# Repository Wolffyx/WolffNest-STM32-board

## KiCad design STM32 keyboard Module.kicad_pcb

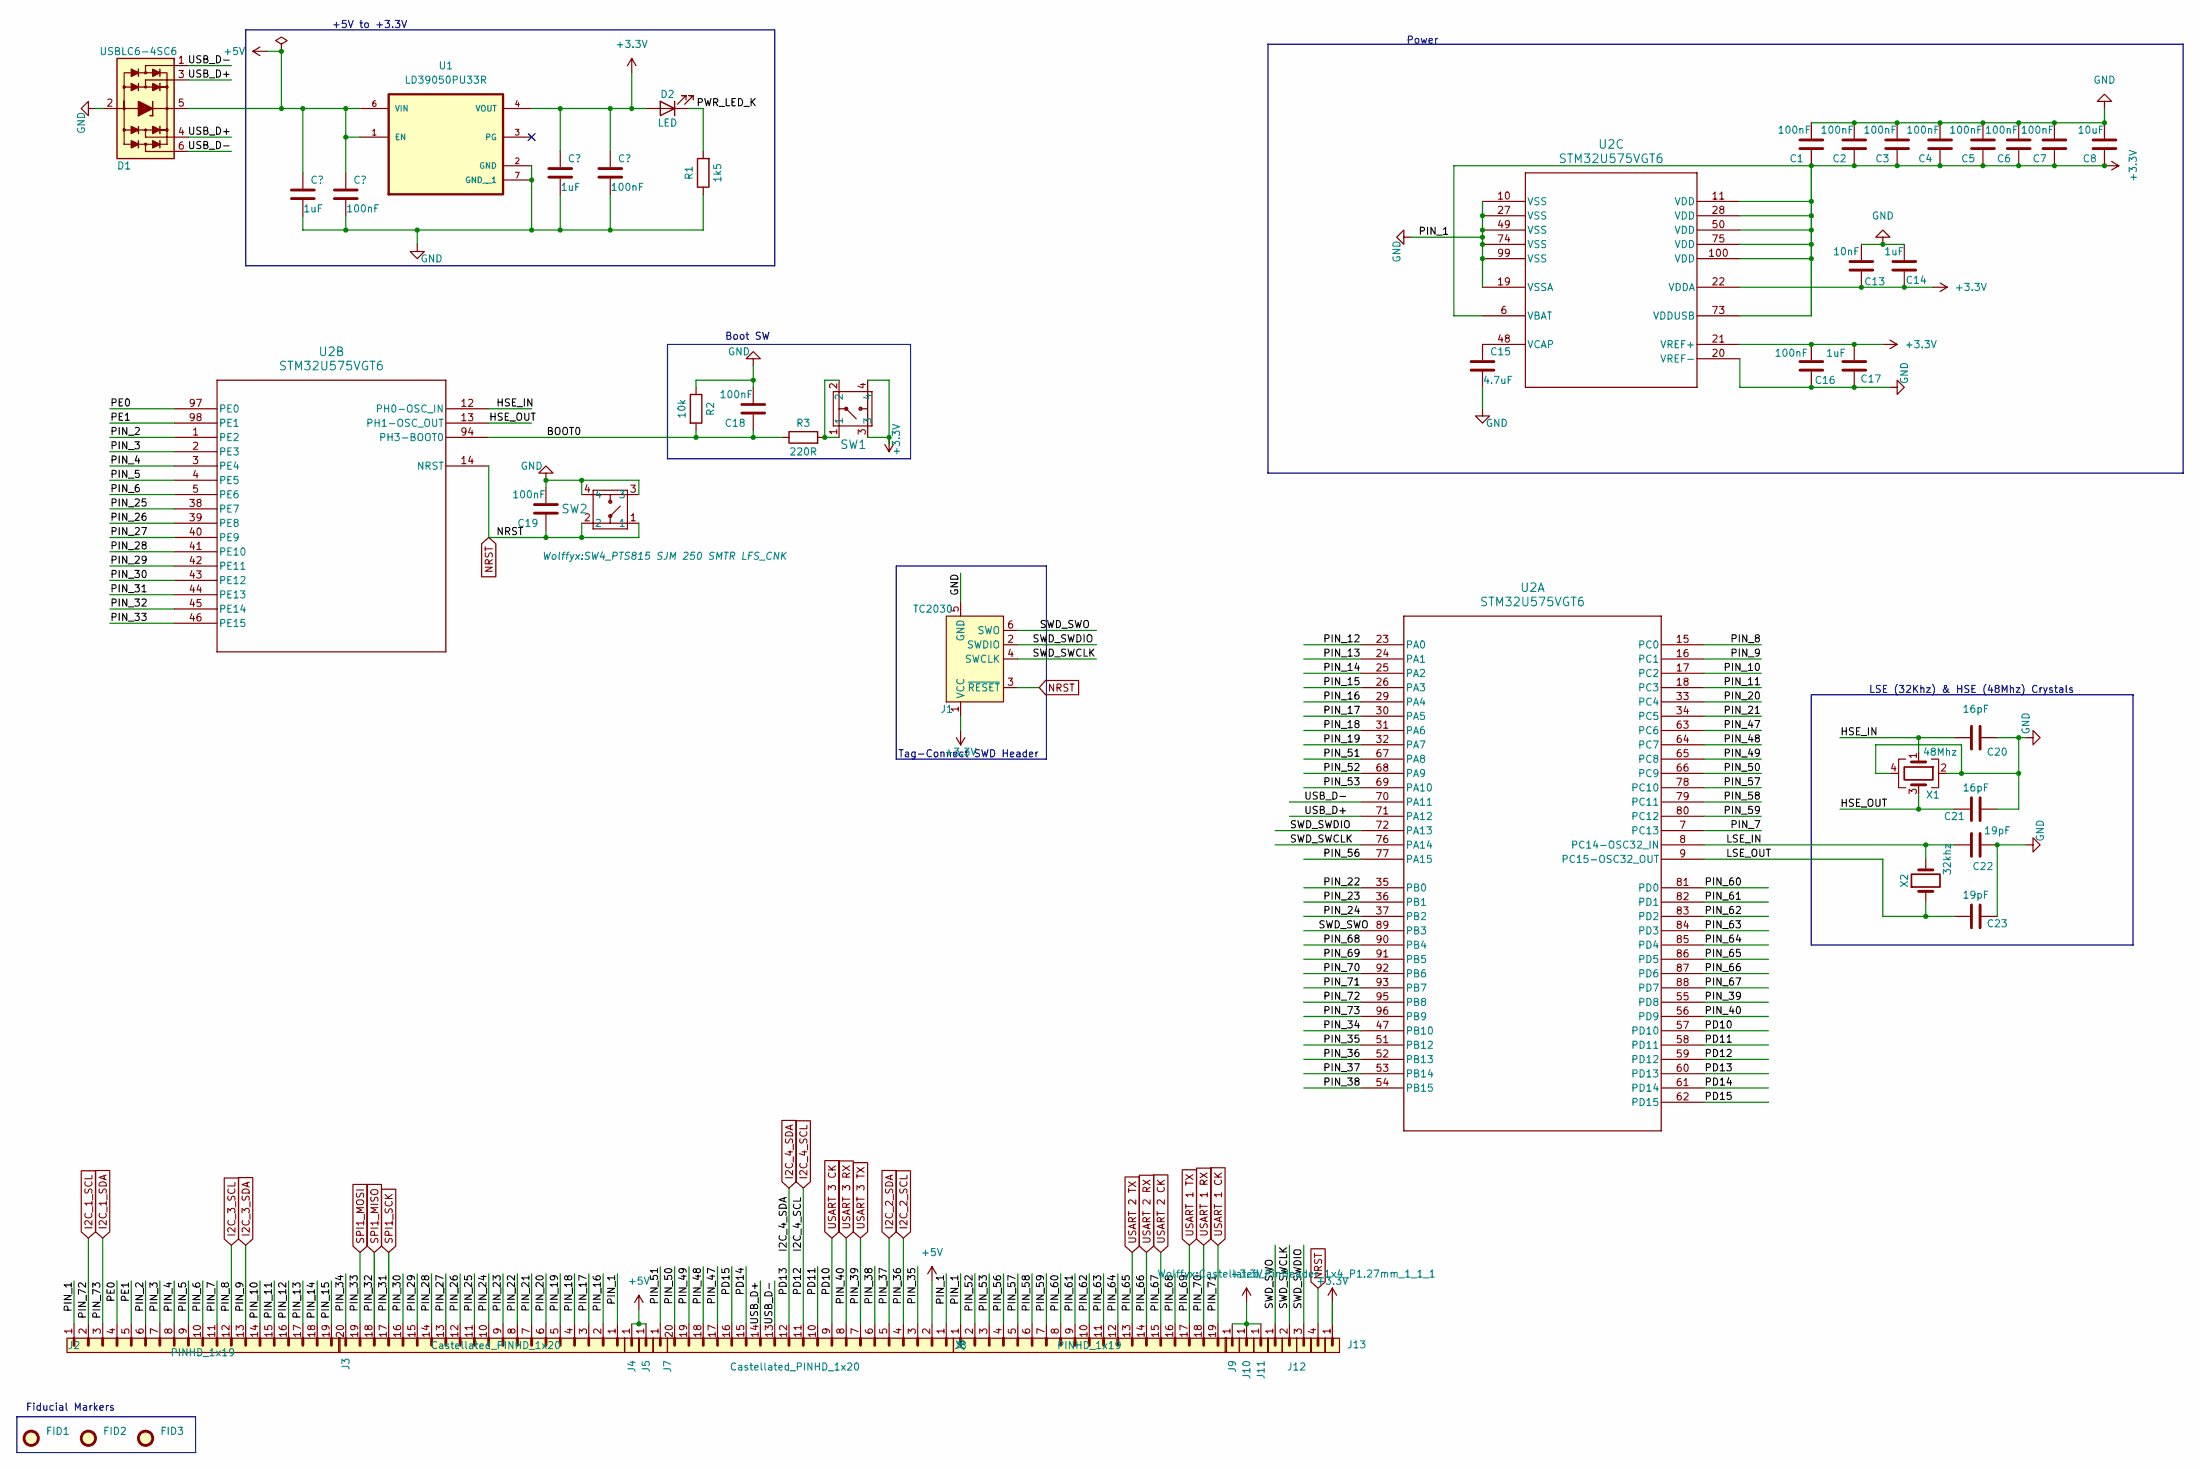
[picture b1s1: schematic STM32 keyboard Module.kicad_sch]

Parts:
C1, C2, C3, C4, C5, C6, C7, C10, C12, C16, C18, C19: 100nF; C_0402_1005Metric; Manufacturer Part No 0402ZD104KAT2A
C8: 10uF; C_0603_1608Metric; Manufacturer Part No CL10A106MQ8NNNC
C9, C11, C14: 1uF; C_0603_1608Metric; Manufacturer Part No CL10B105KQ8NNNC
C13: 10nF; C_0603_1608Metric; Manufacturer Part No CL10B103KB85PND
C15: 4.7uF; C_0603_1608Metric; Manufacturer Part No CL10A475KO8NNNC
C17: 1uF; C_0603_1608Metric; Manufacturer Part No CL10A106MQ8NNNC
C20, C21: 16pF; C_0402_1005Metric; Manufacturer Part No GCM1555C1H160FA16D
C22, C23: 19pF; C_0402_1005Metric; Manufacturer Part No GJM1555C1H190FB01D
D1: USBLC6-4SC6; SOT23-6L_STM; Manufacturer Part No USBLC6-4SC6
D2: LED; LED_0402_1005Metric; Manufacturer Part No SML-P12VTT86R
FID1, FID2, FID3: Fiducial; Fiducial_0.5mm_Mask1.5mm
J1: TC2030; Tag-Connect_TC2030-IDC-NL_2x03_P1.27mm_Vertical
J2, J8: PINHD_1x19; Castellated_PinHeader_1x19_P1.27mm
J3, J6: Castellated_PINHD_1x20; Castellated_PinHeader_1x20_P1.27mm
J4, J5, J7, J9, J10, J11: PINHD_1x1; Castellated_PinHeader_1x1_P1.27mm
J12: PINHD_1x4; Castellated_PinHeader_1x4_P1.27mm_1_1_1
J13: PINHD_1x1; Castellated_PinHeader_1x1_P1.27mm_1_1
R1: 1k5; R_0402_1005Metric; Manufacturer Part No 0402WGF1501TCE
R2: 10k; R_0402_1005Metric; Manufacturer Part No RK73B1ETTP103J
R3: 220R; R_0402_1005Metric; Manufacturer Part No RC0402FR-13220RL
SW1, SW2: PTS815 SJM 250 SMTR LFS; SW4_PTS815 SJM 250 SMTR LFS_CNK; Manufacturer Part No PTS815 SJM 250 SMTR LFS
U1: LD39050PU33R; SON95P300X300X100-7N; Manufacturer Part No LD39050PU33R
U2: STM32U575VGT6; LQFP-100_STM
X1: 48Mhz; Crystal_SMD_2016-4Pin_2.0x1.6mm; Manufacturer Part No FA-128 48.0000MF20X-K0
X2: 32khz; Crystal_SMD_2012-2Pin_2.0x1.2mm; Manufacturer Part No ECS-.327-12.5-12R-TR

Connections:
/BOOT0: C18.1, R2.2, R3.1, U2.94 (PH3-BOOT0)
/HSE_IN: C20.1, U2.12 (PH0-OSC_IN), X1.1
/HSE_OUT: C21.1, U2.13 (PH1-OSC_OUT), X1.3
/LSE_IN: C22.1, U2.8 (PC14-OSC32_IN), X2.2
/LSE_OUT: C23.1, U2.9 (PC15-OSC32_OUT), X2.1
/PD11: J6.10, U2.58 (PD11)
/PD14: J6.15, U2.61 (PD14)
/PD15: J6.16, U2.62 (PD15)
/PE0: J2.4, U2.97 (PE0)
/PE1: J2.5, U2.98 (PE1)
/PIN_2: J2.6, U2.1 (PE2)
/PIN_3: J2.7, U2.2 (PE3)
/PIN_4: J2.8, U2.3 (PE4)
/PIN_5: J2.9, U2.4 (PE5)
/PIN_6: J2.10, U2.5 (PE6)
/PIN_7: J2.11, U2.7 (PC13)
/PIN_10: J2.14, U2.17 (PC2)
/PIN_11: J2.15, U2.18 (PC3)
/PIN_12: J2.16, U2.23 (PA0)
/PIN_13: J2.17, U2.24 (PA1)
/PIN_14: J2.18, U2.25 (PA2)
/PIN_15: J2.19, U2.26 (PA3)
/PIN_16: J3.2, U2.29 (PA4)
/PIN_17: J3.3, U2.30 (PA5)
/PIN_18: J3.4, U2.31 (PA6)
/PIN_19: J3.5, U2.32 (PA7)
/PIN_20: J3.6, U2.33 (PC4)
/PIN_21: J3.7, U2.34 (PC5)
/PIN_22: J3.8, U2.35 (PB0)
/PIN_23: J3.9, U2.36 (PB1)
/PIN_24: J3.10, U2.37 (PB2)
/PIN_25: J3.11, U2.38 (PE7)
/PIN_26: J3.12, U2.39 (PE8)
/PIN_27: J3.13, U2.40 (PE9)
/PIN_28: J3.14, U2.41 (PE10)
/PIN_29: J3.15, U2.42 (PE11)
/PIN_30: J3.16, U2.43 (PE12)
/PIN_34: J3.20, U2.47 (PB10)
/PIN_35: J6.3, U2.51 (PB12)
/PIN_38: J6.6, U2.54 (PB15)
/PIN_47: J6.17, U2.63 (PC6)
/PIN_48: J6.18, U2.64 (PC7)
/PIN_49: J6.19, U2.65 (PC8)
/PIN_50: J6.20, U2.66 (PC9)
/PIN_51: J7.1, U2.67 (PA8)
/PIN_52: J8.2, U2.68 (PA9)
/PIN_53: J8.3, U2.69 (PA10)
/PIN_56: J8.4, U2.77 (PA15)
/PIN_57: J8.5, U2.78 (PC10)
/PIN_58: J8.6, U2.79 (PC11)
/PIN_59: J8.7, U2.80 (PC12)
/PIN_60: J8.8, U2.81 (PD0)
/PIN_61: J8.9, U2.82 (PD1)
/PIN_62: J8.10, U2.83 (PD2)
/PIN_63: J8.11, U2.84 (PD3)
/PIN_64: J8.12, U2.85 (PD4)
/PIN_68: J8.16, U2.90 (PB4)
/PWR_LED_K: D2.1 (K), R1.2
/SWD_SWCLK: J1.4 (SWCLK), J12.2, U2.76 (PA14)
/SWD_SWDIO: J1.2 (SWDIO), J12.3, U2.72 (PA13)
/SWD_SWO: J1.6 (SWO), J12.1, U2.89 (PB3)
/USB_D+: D1.3 (L2), D1.4 (L3), J6.14, U2.71 (PA12)
/USB_D-: D1.1 (L1), D1.6 (L4), J6.13, U2.70 (PA11)
GND: C1.2, C2.2, C3.2, C4.2, C5.2, C6.2, C7.2, C8.2, C9.2, C10.2, C11.2, C12.2, C13.2, C14.2, C15.2, C16.2, C17.2, C18.2, C19.2, C20.2, C21.2, C22.2, C23.2, D1.2 (VN), J1.5 (GND), J2.1, J3.1, J6.1, J8.1, R1.1, R2.1, SW2.3, SW2.4, U1.2 (GND), U1.7 (GND__1), U2.10 (VSS), U2.19 (VSSA), U2.20 (VREF-), U2.27 (VSS), U2.49 (VSS), U2.74 (VSS), U2.99 (VSS), X1.2, X1.4
I2C_1_SCL: J2.2, U2.95 (PB8)
I2C_1_SDA: J2.3, U2.96 (PB9)
I2C_2_SCL: J6.4, U2.52 (PB13)
I2C_2_SDA: J6.5, U2.53 (PB14)
I2C_3_SCL: J2.12, U2.15 (PC0)
I2C_3_SDA: J2.13, U2.16 (PC1)
I2C_4_SCL: J6.11, U2.59 (PD12)
I2C_4_SDA: J6.12, U2.60 (PD13)
NRST: C19.1, J1.3 (~RESET), J12.4, SW2.1, SW2.2, U2.14 (NRST)
unnamed: R3.2, SW1.1, SW1.2
unnamed: C15.1, U2.48 (VCAP)
SPI1_MISO: J3.18, U2.45 (PE14)
SPI1_MOSI: J3.19, U2.46 (PE15)
SPI1_SCK: J3.17, U2.44 (PE13)
USART 1 CK: J8.19, U2.93 (PB7)
USART 1 RX: J8.18, U2.92 (PB6)
USART 1 TX: J8.17, U2.91 (PB5)
USART 2 CK: J8.15, U2.88 (PD7)
USART 2 RX: J8.14, U2.87 (PD6)
USART 2 TX: J8.13, U2.86 (PD5)
USART 3 CK: J6.9, U2.57 (PD10)
USART 3 RX: J6.8, U2.56 (PD9)
USART 3 TX: J6.7, U2.55 (PD8)

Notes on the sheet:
Tag-Connect SWD Header
Power
Boot SW
+5V to +3.3V
Fiducial Markers
LSE (32Khz) & HSE (48Mhz) Crystals

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
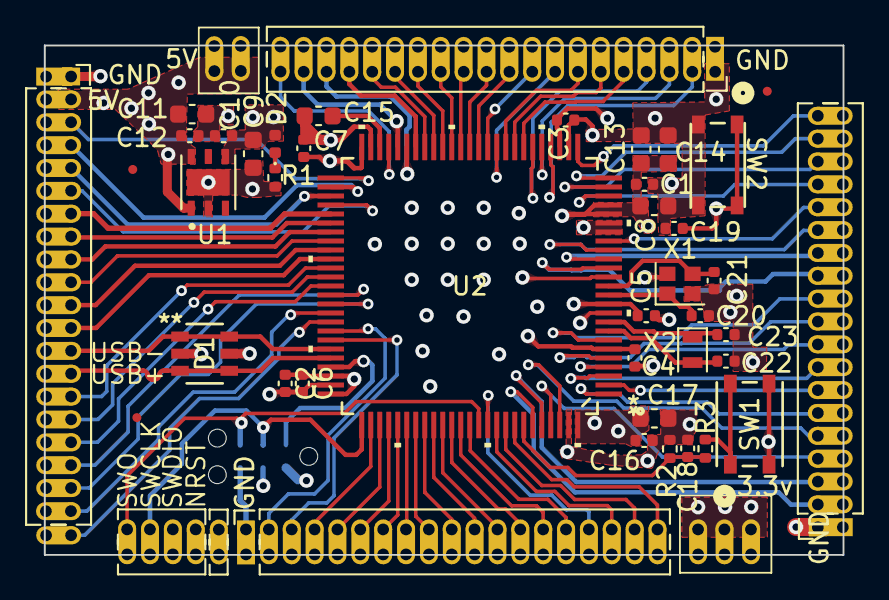
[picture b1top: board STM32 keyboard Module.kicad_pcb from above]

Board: 4 copper layers, 44.4 x 28.3 mm, 50 parts (1 on the bottom side), 89 nets.

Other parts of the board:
J11#2: PINHD_1x1; Castellated_PinHeader_1x1_P1.27mm

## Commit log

2024-07-22 Second commit
2024-07-26 Board v2
2024-07-26 Create LICENSE
